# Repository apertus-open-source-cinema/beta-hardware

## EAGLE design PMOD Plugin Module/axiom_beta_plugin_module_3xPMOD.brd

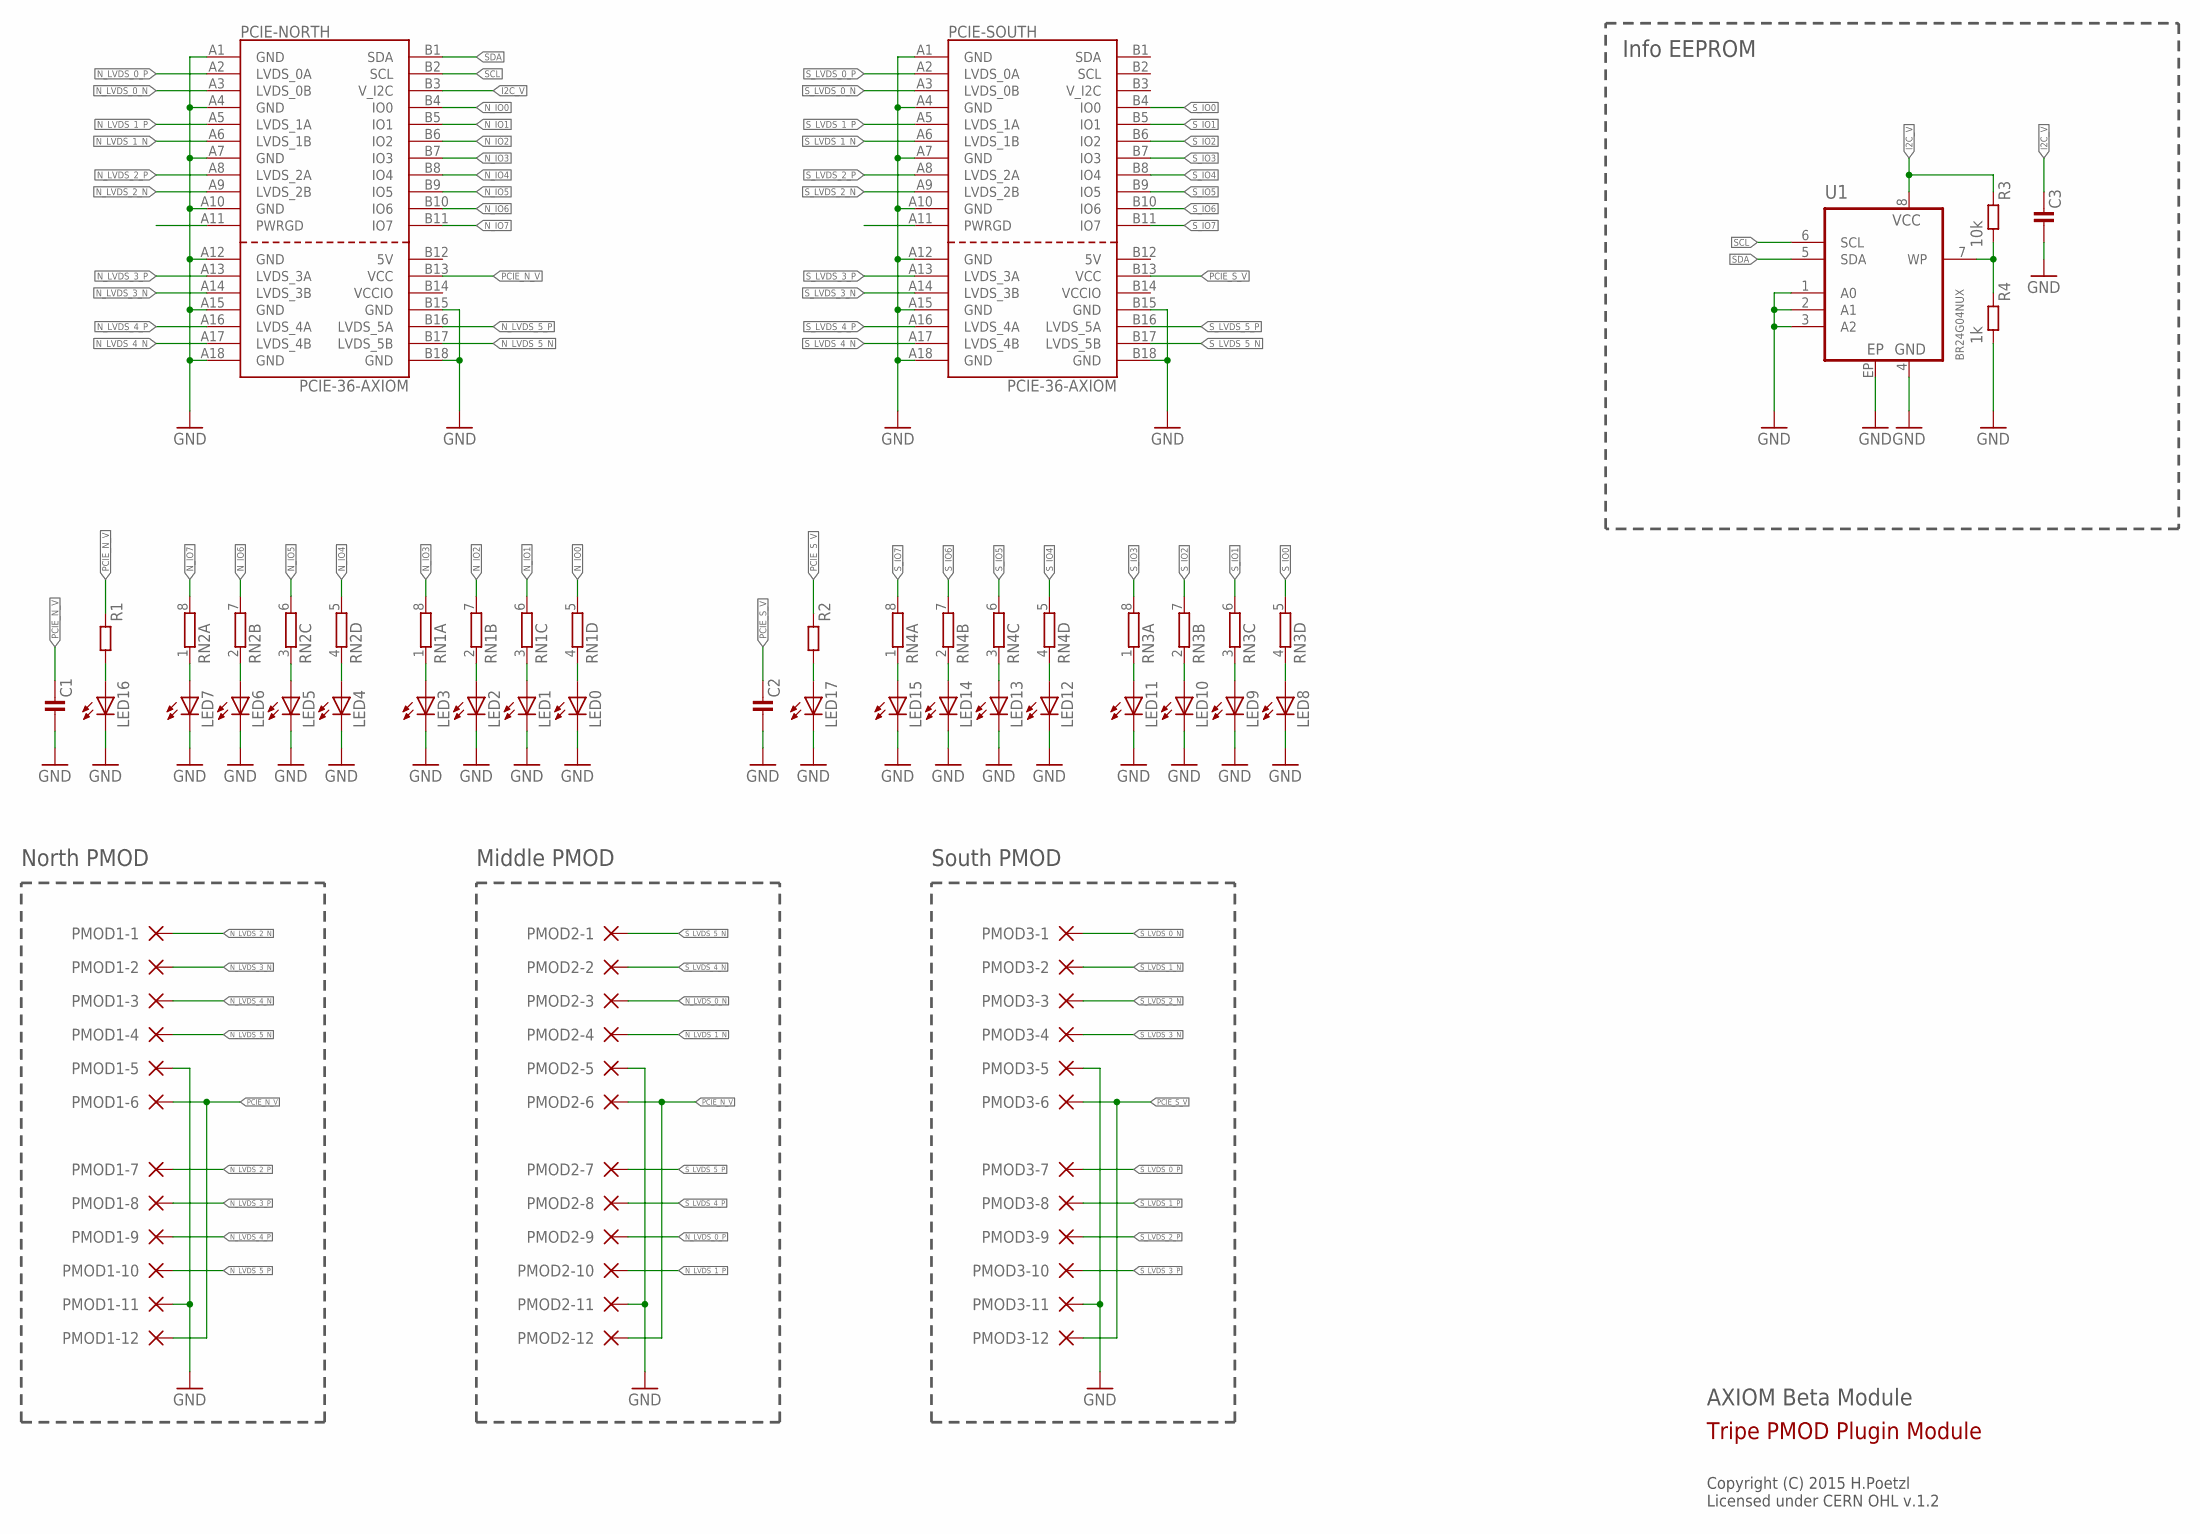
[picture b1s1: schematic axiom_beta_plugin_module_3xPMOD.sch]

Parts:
C1, C2: C1206-A; 1206-A
C3: C0402-B; 0402-B
LED0, LED1, LED2, LED3, LED4, LED5, LED6, LED7, LED8, LED9, LED10, LED11, LED12, LED13, LED14, LED15, LED16, LED17: LEDCHIPLED_0603; CHIPLED_0603
PCIE-NORTH: PCIE-36-AXIOM
PCIE-SOUTH: PCIE-36-AXIOM
PMOD1-1, PMOD1-2, PMOD1-3, PMOD1-4, PMOD1-5, PMOD1-6, PMOD1-7, PMOD1-8, PMOD1-9, PMOD1-10, PMOD1-11, PMOD1-12, PMOD2-1, PMOD2-2, PMOD2-3, PMOD2-4, PMOD2-5, PMOD2-6, PMOD2-7, PMOD2-8, PMOD2-9, PMOD2-10, PMOD2-11, PMOD2-12, PMOD3-1, PMOD3-2, PMOD3-3, PMOD3-4, PMOD3-5, PMOD3-6, PMOD3-7, PMOD3-8, PMOD3-9, PMOD3-10, PMOD3-11, PMOD3-12: SMD-PAD1.6X3.8MM-U; 1.6X3.8U-MM
R1, R2: R0402-B; 0402-B
R3: 10k; 0402-B
R4: 1k; 0402-B
RN1, RN2, RN3, RN4: 4R-NCAY16; CAY16
U1: BR24G04NUX; DFN200X300X100-9N

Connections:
GND: C1.2, C2.2, C3.2, LED0.C, LED1.C, LED2.C, LED3.C, LED4.C, LED5.C, LED6.C, LED7.C, LED8.C, LED9.C, LED10.C, LED11.C, LED12.C, LED13.C, LED14.C, LED15.C, LED16.C, LED17.C, PCIE-NORTH.A1 (GND), PCIE-NORTH.A4 (GND), PCIE-NORTH.A7 (GND), PCIE-NORTH.A10 (GND), PCIE-NORTH.A12 (GND), PCIE-NORTH.A15 (GND), PCIE-NORTH.A18 (GND), PCIE-NORTH.B15 (GND), PCIE-NORTH.B18 (GND), PCIE-SOUTH.A1 (GND), PCIE-SOUTH.A4 (GND), PCIE-SOUTH.A7 (GND), PCIE-SOUTH.A10 (GND), PCIE-SOUTH.A12 (GND), PCIE-SOUTH.A15 (GND), PCIE-SOUTH.A18 (GND), PCIE-SOUTH.B15 (GND), PCIE-SOUTH.B18 (GND), PMOD1-5.1, PMOD1-11.1, PMOD2-5.1, PMOD2-11.1, PMOD3-5.1, PMOD3-11.1, R4.2, U1.1 (A0), U1.2 (A1), U1.3 (A2), U1.4 (GND), U1.EP
I2C_V: C3.1, PCIE-NORTH.B3 (V_I2C), R3.1, U1.8 (VCC)
unnamed: LED3.A, RN1.1
unnamed: LED2.A, RN1.2 (1)
unnamed: LED1.A, RN1.3 (1)
unnamed: LED0.A, RN1.4 (1)
unnamed: LED16.A, R1.2
unnamed: LED17.A, R2.2
unnamed: R3.2, R4.1, U1.7 (WP)
unnamed: LED7.A, RN2.1
unnamed: LED6.A, RN2.2 (1)
unnamed: LED5.A, RN2.3 (1)
unnamed: LED4.A, RN2.4 (1)
unnamed: LED11.A, RN3.1
unnamed: LED10.A, RN3.2 (1)
unnamed: LED9.A, RN3.3 (1)
unnamed: LED8.A, RN3.4 (1)
unnamed: LED15.A, RN4.1
unnamed: LED14.A, RN4.2 (1)
unnamed: LED13.A, RN4.3 (1)
unnamed: LED12.A, RN4.4 (1)
N_IO0: PCIE-NORTH.B4 (IO0), RN1.5 (2)
N_IO1: PCIE-NORTH.B5 (IO1), RN1.6 (2)
N_IO2: PCIE-NORTH.B6 (IO2), RN1.7 (2)
N_IO3: PCIE-NORTH.B7 (IO3), RN1.8 (2)
N_IO4: PCIE-NORTH.B8 (IO4), RN2.5 (2)
N_IO5: PCIE-NORTH.B9 (IO5), RN2.6 (2)
N_IO6: PCIE-NORTH.B10 (IO6), RN2.7 (2)
N_IO7: PCIE-NORTH.B11 (IO7), RN2.8 (2)
N_LVDS_0_N: PCIE-NORTH.A3 (LVDS_0B), PMOD2-3.1
N_LVDS_0_P: PCIE-NORTH.A2 (LVDS_0A), PMOD2-9.1
N_LVDS_1_N: PCIE-NORTH.A6 (LVDS_1B), PMOD2-4.1
N_LVDS_1_P: PCIE-NORTH.A5 (LVDS_1A), PMOD2-10.1
N_LVDS_2_N: PCIE-NORTH.A9 (LVDS_2B), PMOD1-1.1
N_LVDS_2_P: PCIE-NORTH.A8 (LVDS_2A), PMOD1-7.1
N_LVDS_3_N: PCIE-NORTH.A14 (LVDS_3B), PMOD1-2.1
N_LVDS_3_P: PCIE-NORTH.A13 (LVDS_3A), PMOD1-8.1
N_LVDS_4_N: PCIE-NORTH.A17 (LVDS_4B), PMOD1-3.1
N_LVDS_4_P: PCIE-NORTH.A16 (LVDS_4A), PMOD1-9.1
N_LVDS_5_N: PCIE-NORTH.B17 (LVDS_5B), PMOD1-4.1
N_LVDS_5_P: PCIE-NORTH.B16 (LVDS_5A), PMOD1-10.1
PCIE_N_V: C1.1, PCIE-NORTH.B13 (VCC), PMOD1-6.1, PMOD1-12.1, PMOD2-6.1, PMOD2-12.1, R1.1
PCIE_S_V: C2.1, PCIE-SOUTH.B13 (VCC), PMOD3-6.1, PMOD3-12.1, R2.1
SCL: PCIE-NORTH.B2 (SCL), U1.6 (SCL)
SDA: PCIE-NORTH.B1 (SDA), U1.5 (SDA)
S_IO0: PCIE-SOUTH.B4 (IO0), RN3.5 (2)
S_IO1: PCIE-SOUTH.B5 (IO1), RN3.6 (2)
S_IO2: PCIE-SOUTH.B6 (IO2), RN3.7 (2)
S_IO3: PCIE-SOUTH.B7 (IO3), RN3.8 (2)
S_IO4: PCIE-SOUTH.B8 (IO4), RN4.5 (2)
S_IO5: PCIE-SOUTH.B9 (IO5), RN4.6 (2)
S_IO6: PCIE-SOUTH.B10 (IO6), RN4.7 (2)
S_IO7: PCIE-SOUTH.B11 (IO7), RN4.8 (2)
S_LVDS_0_N: PCIE-SOUTH.A3 (LVDS_0B), PMOD3-1.1
S_LVDS_0_P: PCIE-SOUTH.A2 (LVDS_0A), PMOD3-7.1
S_LVDS_1_N: PCIE-SOUTH.A6 (LVDS_1B), PMOD3-2.1
S_LVDS_1_P: PCIE-SOUTH.A5 (LVDS_1A), PMOD3-8.1
S_LVDS_2_N: PCIE-SOUTH.A9 (LVDS_2B), PMOD3-3.1
S_LVDS_2_P: PCIE-SOUTH.A8 (LVDS_2A), PMOD3-9.1
S_LVDS_3_N: PCIE-SOUTH.A14 (LVDS_3B), PMOD3-4.1
S_LVDS_3_P: PCIE-SOUTH.A13 (LVDS_3A), PMOD3-10.1
S_LVDS_4_N: PCIE-SOUTH.A17 (LVDS_4B), PMOD2-2.1
S_LVDS_4_P: PCIE-SOUTH.A16 (LVDS_4A), PMOD2-8.1
S_LVDS_5_N: PCIE-SOUTH.B17 (LVDS_5B), PMOD2-1.1
S_LVDS_5_P: PCIE-SOUTH.B16 (LVDS_5A), PMOD2-7.1

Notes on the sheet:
AXIOM Beta Module
Copyright (C) 2015 H.Poetzl Licensed under CERN OHL v.1.2
Tripe PMOD Plugin Module
Info EEPROM
North PMOD
Middle PMOD
South PMOD

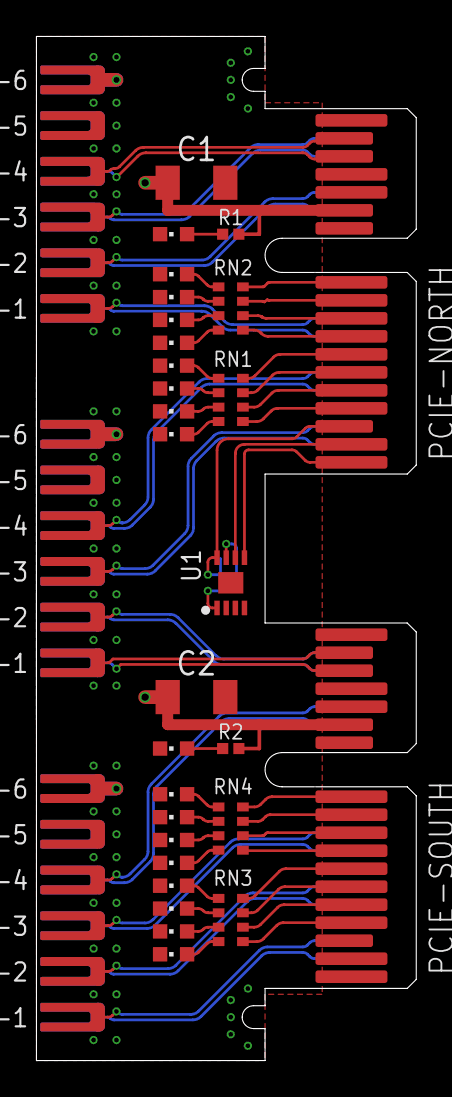
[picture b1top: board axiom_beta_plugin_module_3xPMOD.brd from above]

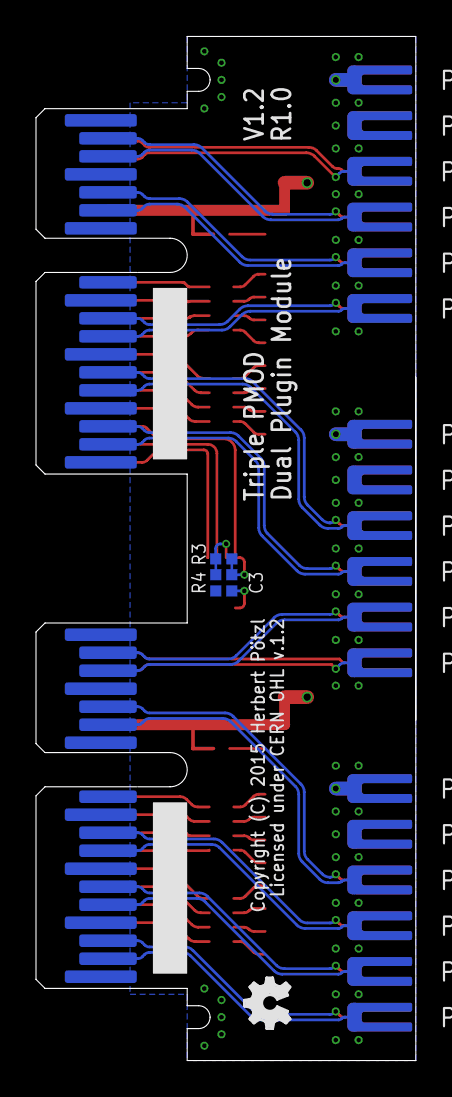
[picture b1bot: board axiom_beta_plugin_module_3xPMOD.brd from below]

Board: 4 copper layers, 21.1 x 56.9 mm, 69 parts (22 on the bottom side), 65 nets.

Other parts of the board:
LOGO1: OSHW_LOGO_FILLX0100-NT; OSHW_FILLX100_NOTEXT

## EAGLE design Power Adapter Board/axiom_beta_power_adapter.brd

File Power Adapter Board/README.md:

# AXIOM Beta Power Adapter Board v0.2

https://wiki.apertus.org/index.php/Beta_Power_Adapter_Board

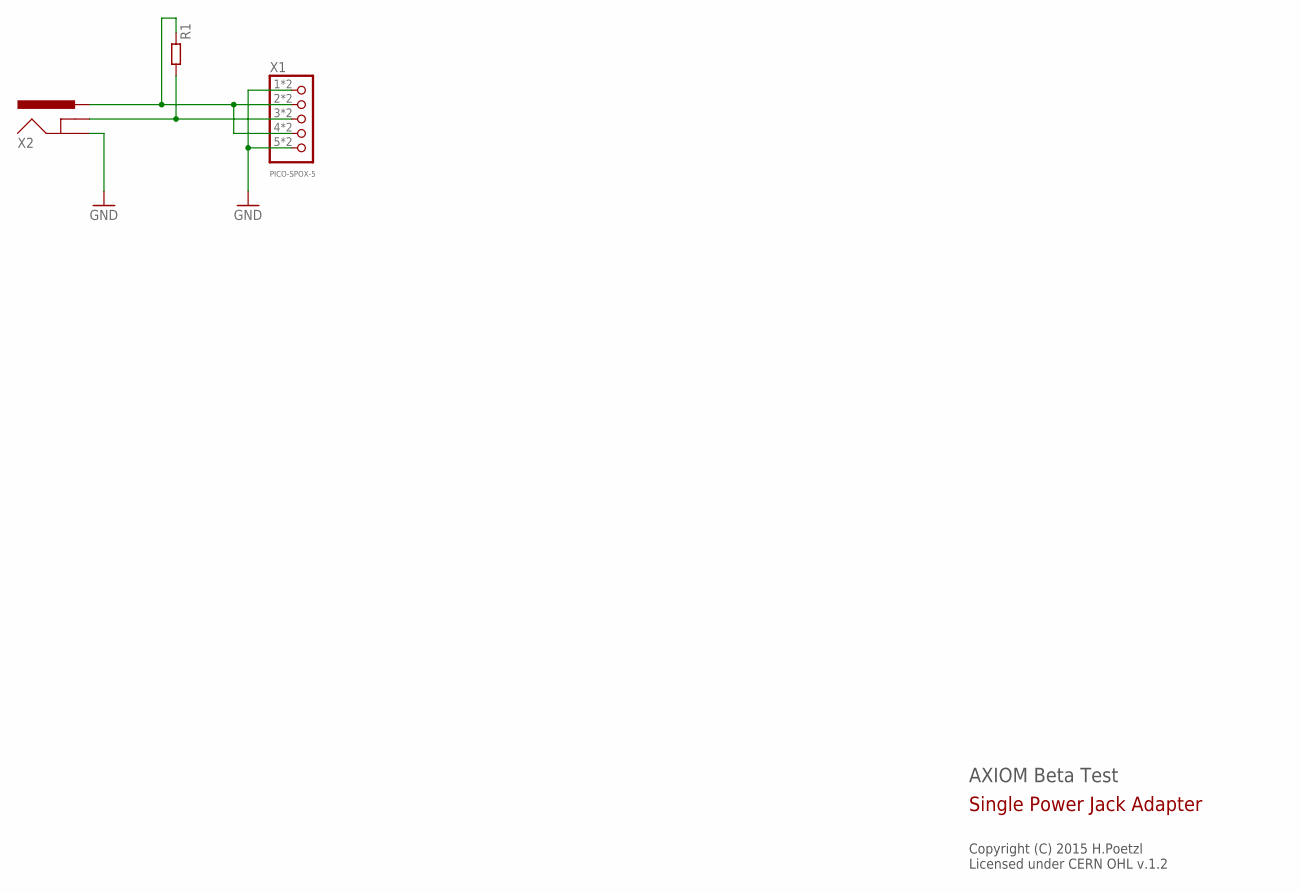
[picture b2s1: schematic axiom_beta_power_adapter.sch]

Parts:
R1: R0402-B; 0402-B
X1: PICO-SPOX-5
X2: POWER_JACKPTH_N; POWER_JACK_PTH_NARROW

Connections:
BETA_5V: R1.1, X1.2, X1.2A (2), X1.4, X1.4A (4), X2.PWR
GND: X1.1, X1.1A (1), X1.5, X1.5A (5), X2.GND
VIN: R1.2, X1.3, X1.3A (3), X2.SHUNT (GNDBREAK)

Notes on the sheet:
AXIOM Beta Test
Copyright (C) 2015 H.Poetzl Licensed under CERN OHL v.1.2
Single Power Jack Adapter

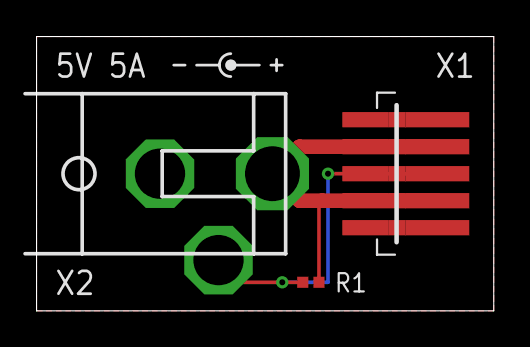
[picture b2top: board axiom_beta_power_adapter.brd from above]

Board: 2 copper layers, 25.4 x 15.2 mm, 4 parts (1 on the bottom side), 3 nets.

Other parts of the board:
LOGO1: OSHW_LOGO_FILLX0100-NT; OSHW_FILLX100_NOTEXT

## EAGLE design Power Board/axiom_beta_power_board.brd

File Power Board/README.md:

# AXIOM Beta Power Board v0.30

https://wiki.apertus.org/index.php/Beta_Power_Board

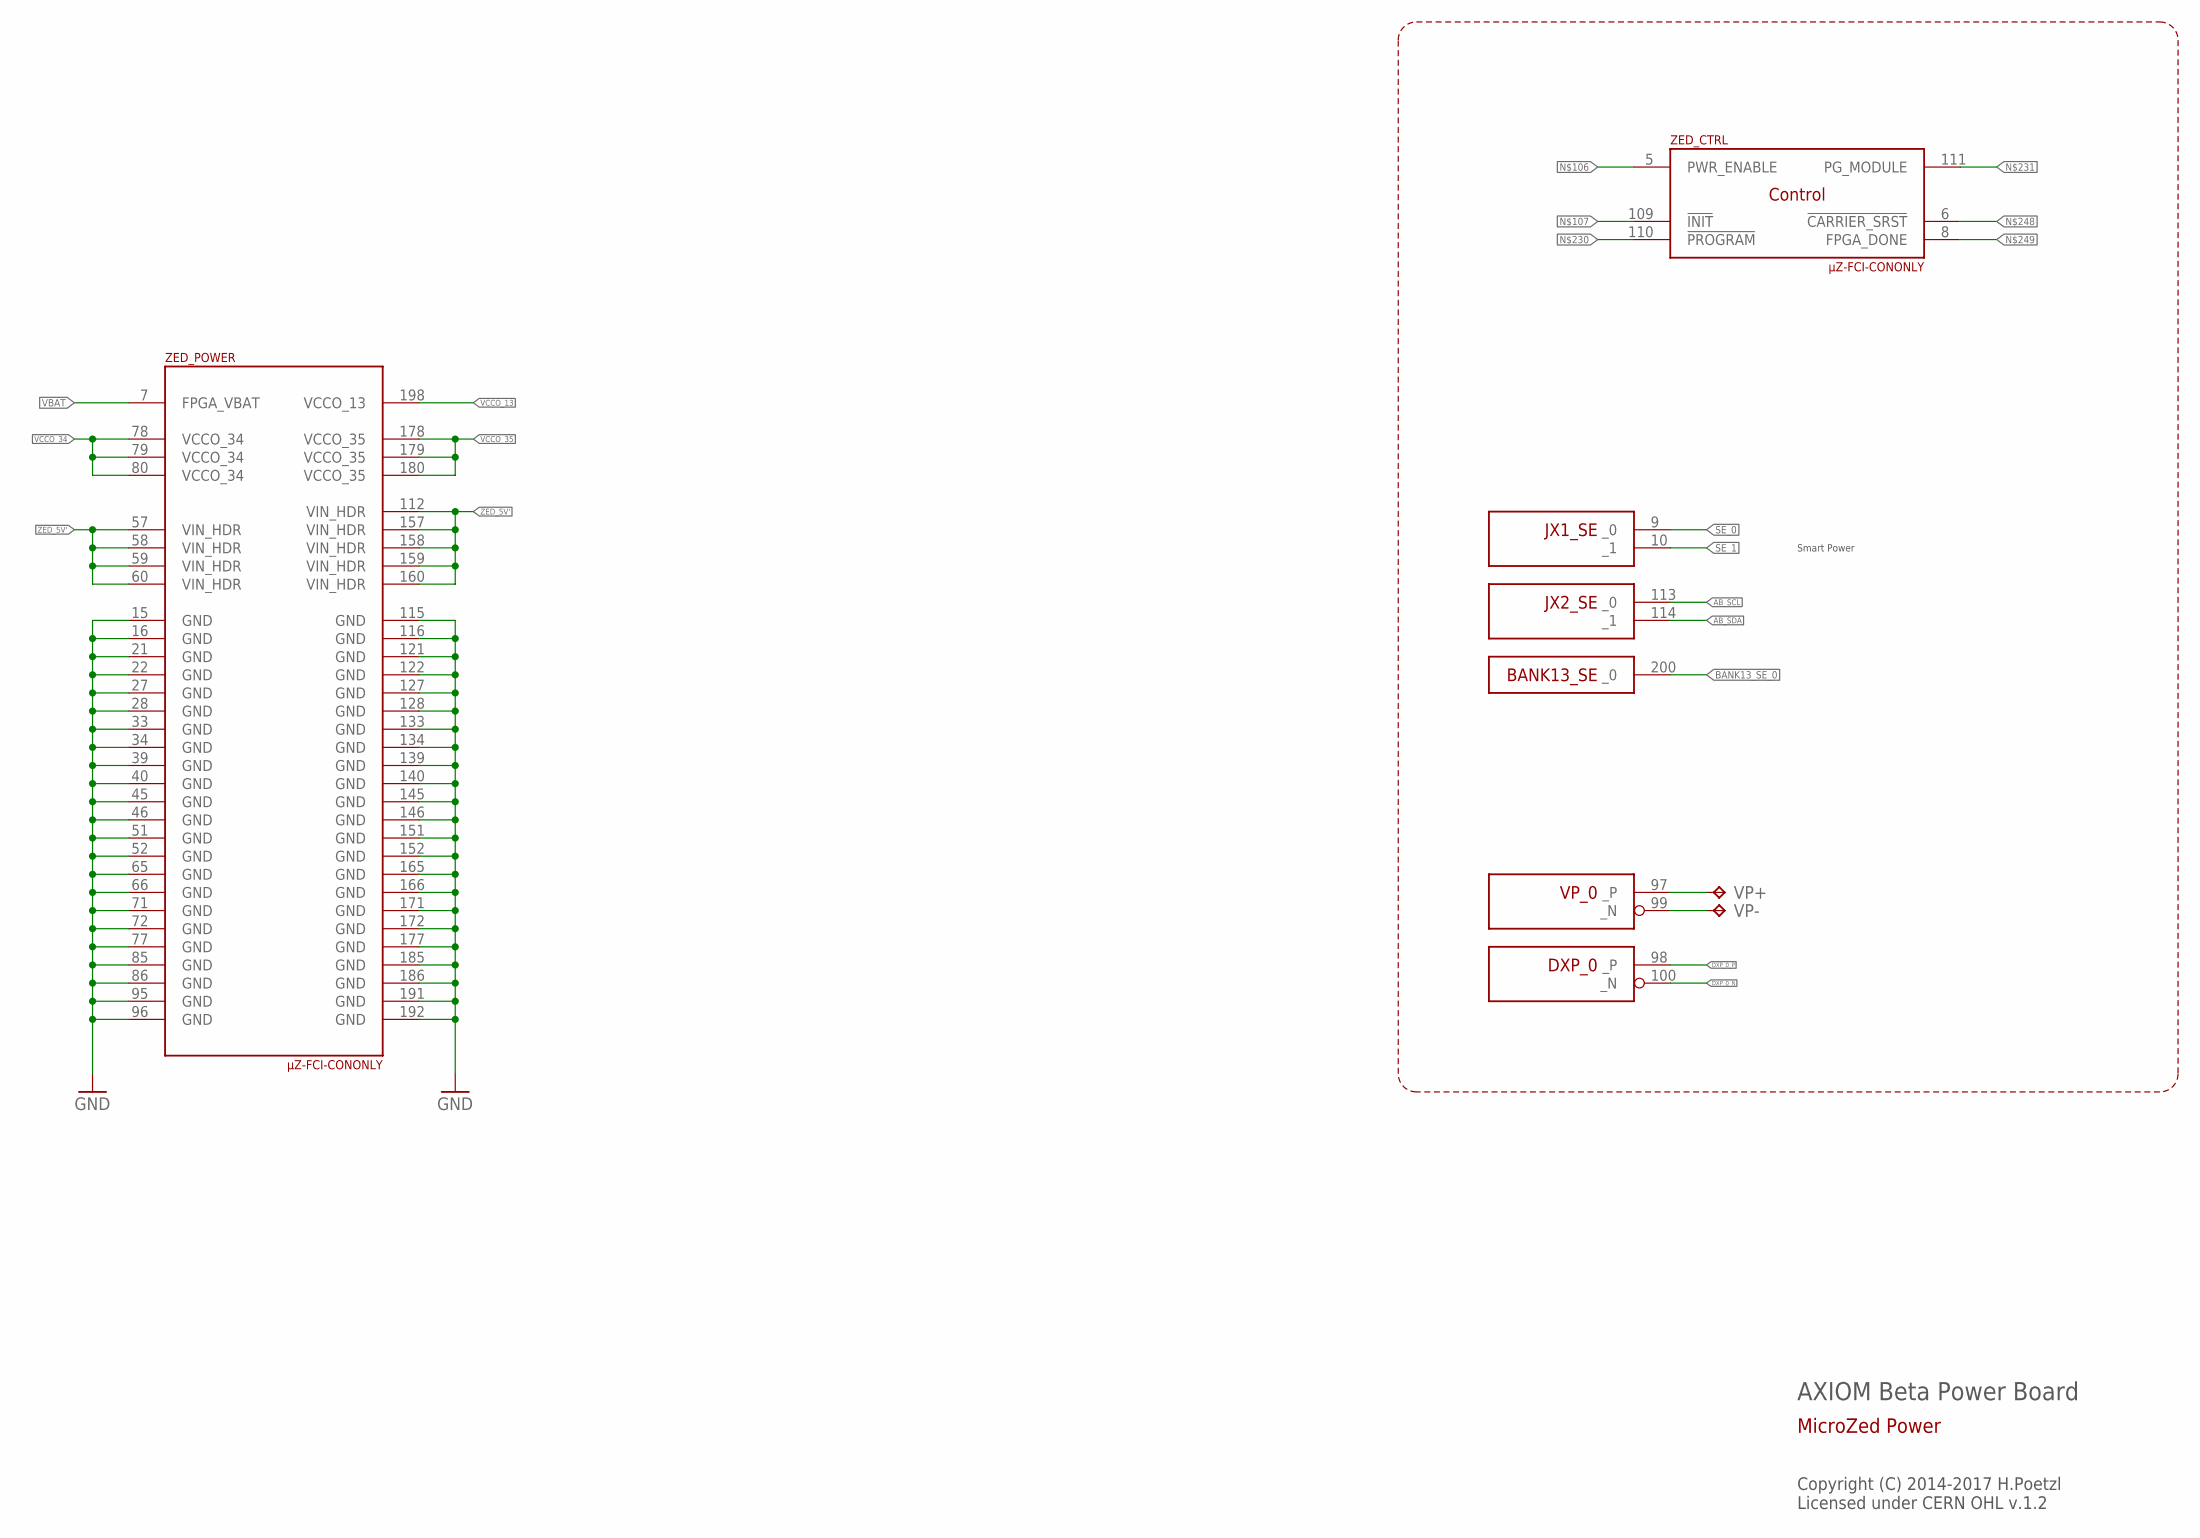
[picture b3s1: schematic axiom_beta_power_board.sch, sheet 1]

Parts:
VP+: TPTP16SQ; TP16SQ
VP-: TPTP16SQ; TP16SQ
ZED: µZ-FCI-CONONLY; µZ-CONONLY

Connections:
AB_SCL: ZED.113 (_0); also elsewhere on the board
AB_SDA: ZED.114 (_1); also elsewhere on the board
BANK13_SE_0: ZED.200 (_0); also elsewhere on the board
DXP_0_N: ZED.100 (_N)
DXP_0_P: ZED.98 (_P)
GND: ZED.15 (GND), ZED.16 (GND), ZED.21 (GND), ZED.22 (GND), ZED.27 (GND), ZED.28 (GND), ZED.33 (GND), ZED.34 (GND), ZED.39 (GND), ZED.40 (GND), ZED.45 (GND), ZED.46 (GND), ZED.51 (GND), ZED.52 (GND), ZED.65 (GND), ZED.66 (GND), ZED.71 (GND), ZED.72 (GND), ZED.77 (GND), ZED.85 (GND), ZED.86 (GND), ZED.95 (GND), ZED.96 (GND), ZED.115 (GND), ZED.116 (GND), ZED.121 (GND), ZED.122 (GND), ZED.127 (GND), ZED.128 (GND), ZED.133 (GND), ZED.134 (GND), ZED.139 (GND), ZED.140 (GND), ZED.145 (GND), ZED.146 (GND), ZED.151 (GND), ZED.152 (GND), ZED.165 (GND), ZED.166 (GND), ZED.171 (GND), ZED.172 (GND), ZED.177 (GND), ZED.185 (GND), ZED.186 (GND), ZED.191 (GND), ZED.192 (GND); also elsewhere on the board
SE_0: ZED.9 (_0); also elsewhere on the board
SE_1: ZED.10 (_1); also elsewhere on the board
VBAT: ZED.7 (FPGA_VBAT)
VCCO_13: ZED.198 (VCCO_13); also elsewhere on the board
VCCO_34: ZED.78 (VCCO_34), ZED.79 (VCCO_34), ZED.80 (VCCO_34); also elsewhere on the board
VCCO_35: ZED.178 (VCCO_35), ZED.179 (VCCO_35), ZED.180 (VCCO_35); also elsewhere on the board
VP_0_N: VP-.TP, ZED.99 (_N)
VP_0_P: VP+.TP, ZED.97 (_P)
ZED_5V': ZED.57 (VIN_HDR), ZED.58 (VIN_HDR), ZED.59 (VIN_HDR), ZED.60 (VIN_HDR), ZED.112 (VIN_HDR), ZED.157 (VIN_HDR), ZED.158 (VIN_HDR), ZED.159 (VIN_HDR), ZED.160 (VIN_HDR); also elsewhere on the board

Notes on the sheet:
AXIOM Beta Power Board
Copyright (C) 2014-2017 H.Poetzl Licensed under CERN OHL v.1.2
MicroZed Power
Smart Power

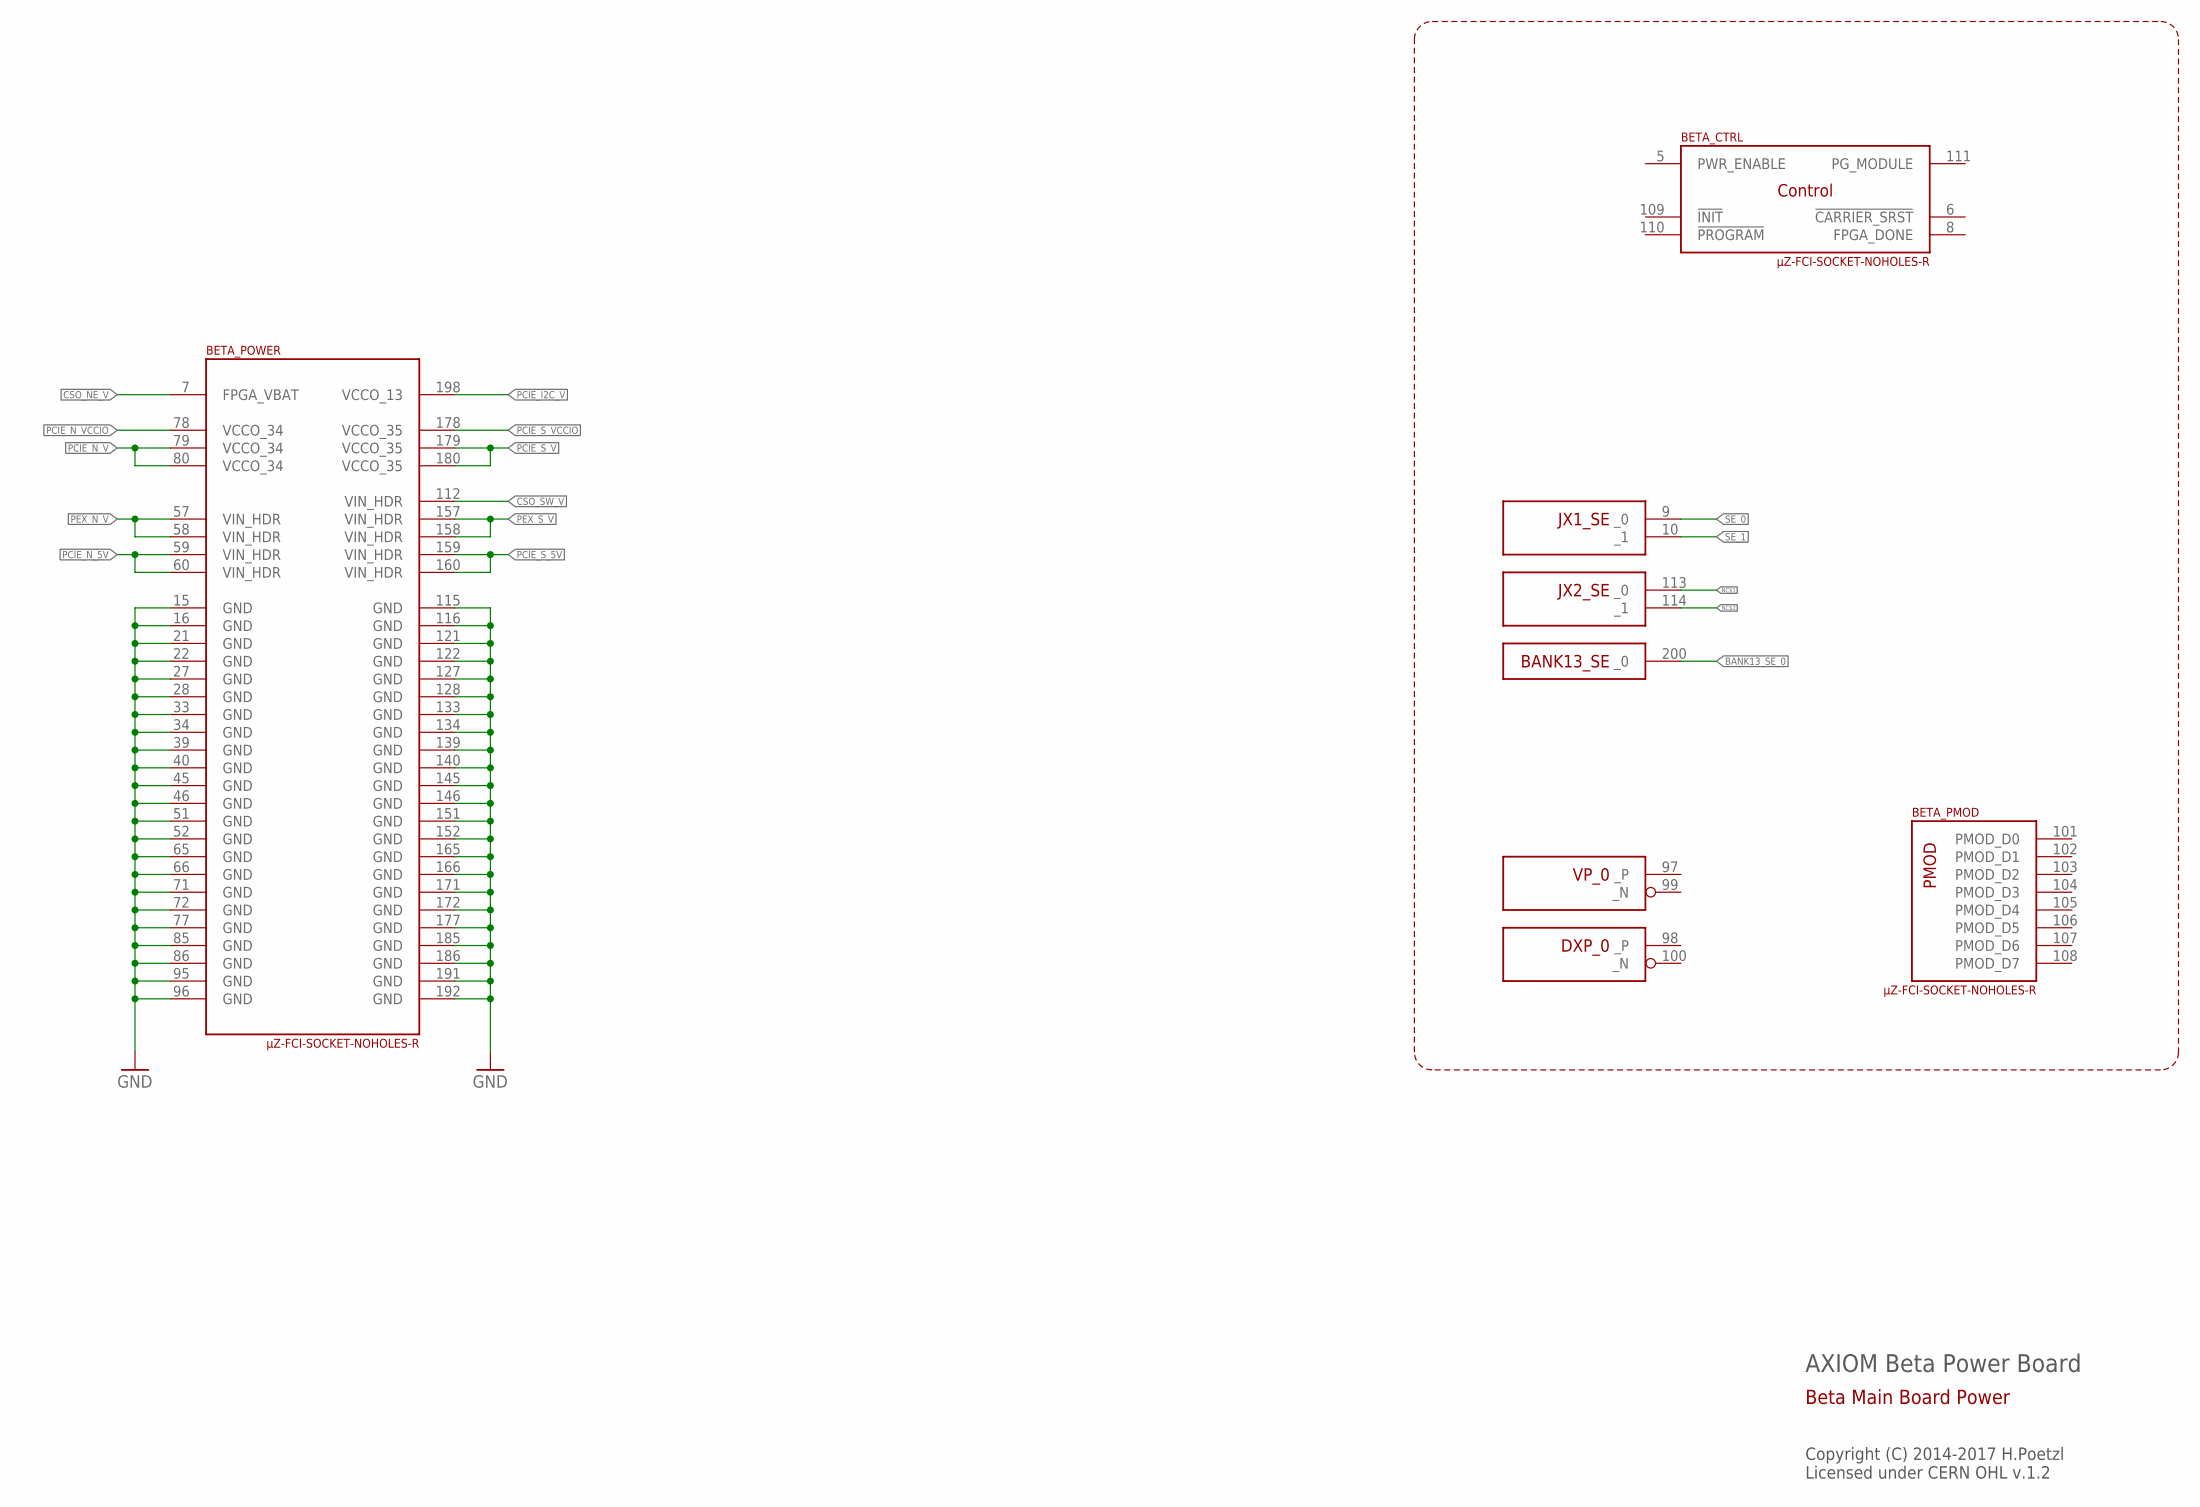
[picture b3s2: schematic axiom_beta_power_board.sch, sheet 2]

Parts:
BETA: µZ-FCI-SOCKET-NOHOLES-R; µZ-SOCKET-NOHOLES-R

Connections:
BANK13_SE_0: BETA.200 (_0); also elsewhere on the board
CSO_NE_V: BETA.7 (FPGA_VBAT); also elsewhere on the board
CSO_SW_V: BETA.112 (VIN_HDR); also elsewhere on the board
GND: BETA.15 (GND), BETA.16 (GND), BETA.21 (GND), BETA.22 (GND), BETA.27 (GND), BETA.28 (GND), BETA.33 (GND), BETA.34 (GND), BETA.39 (GND), BETA.40 (GND), BETA.45 (GND), BETA.46 (GND), BETA.51 (GND), BETA.52 (GND), BETA.65 (GND), BETA.66 (GND), BETA.71 (GND), BETA.72 (GND), BETA.77 (GND), BETA.85 (GND), BETA.86 (GND), BETA.95 (GND), BETA.96 (GND), BETA.115 (GND), BETA.116 (GND), BETA.121 (GND), BETA.122 (GND), BETA.127 (GND), BETA.128 (GND), BETA.133 (GND), BETA.134 (GND), BETA.139 (GND), BETA.140 (GND), BETA.145 (GND), BETA.146 (GND), BETA.151 (GND), BETA.152 (GND), BETA.165 (GND), BETA.166 (GND), BETA.171 (GND), BETA.172 (GND), BETA.177 (GND), BETA.185 (GND), BETA.186 (GND), BETA.191 (GND), BETA.192 (GND); also elsewhere on the board
NC$1: BETA.113 (_0)
NC$2: BETA.114 (_1)
PCIE_I2C_V: BETA.198 (VCCO_13)
PCIE_N_5V: BETA.59 (VIN_HDR), BETA.60 (VIN_HDR)
PCIE_N_V: BETA.79 (VCCO_34), BETA.80 (VCCO_34); also elsewhere on the board
PCIE_N_VCCIO: BETA.78 (VCCO_34)
PCIE_S_5V: BETA.159 (VIN_HDR), BETA.160 (VIN_HDR)
PCIE_S_V: BETA.179 (VCCO_35), BETA.180 (VCCO_35); also elsewhere on the board
PCIE_S_VCCIO: BETA.178 (VCCO_35)
PEX_N_V: BETA.57 (VIN_HDR), BETA.58 (VIN_HDR)
PEX_S_V: BETA.157 (VIN_HDR), BETA.158 (VIN_HDR)
SE_0: BETA.9 (_0); also elsewhere on the board
SE_1: BETA.10 (_1); also elsewhere on the board

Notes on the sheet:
AXIOM Beta Power Board
Copyright (C) 2014-2017 H.Poetzl Licensed under CERN OHL v.1.2
Beta Main Board Power

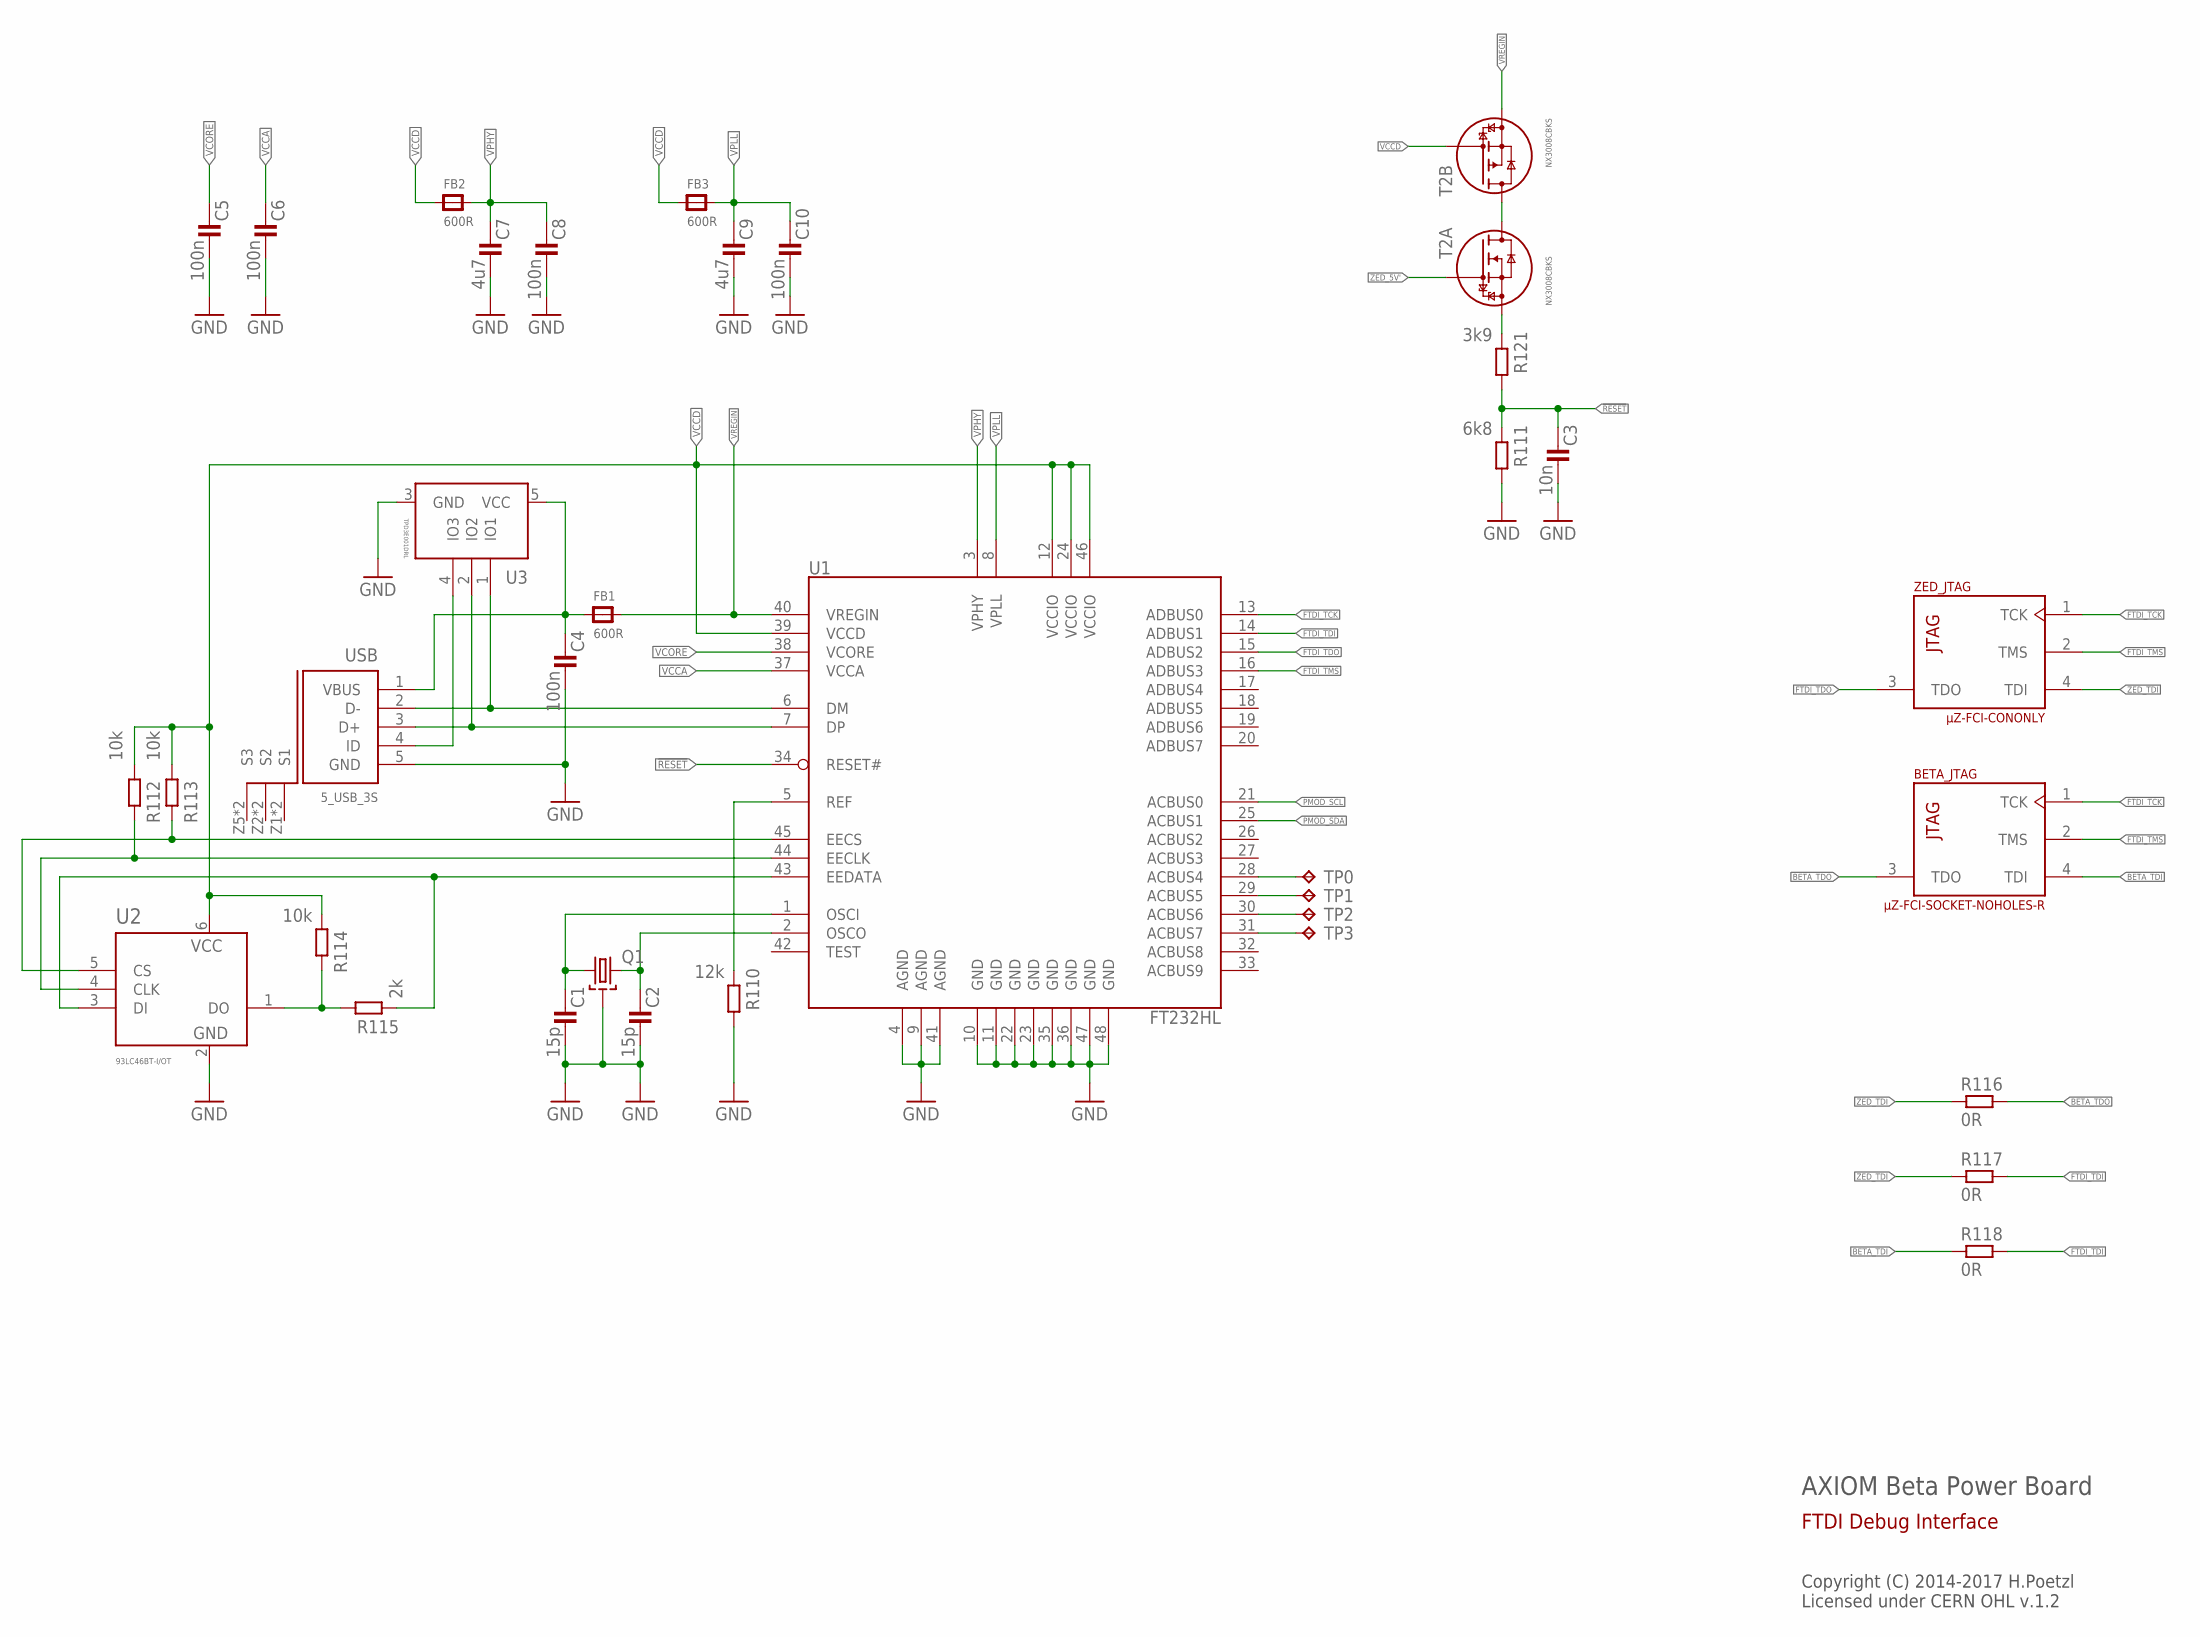
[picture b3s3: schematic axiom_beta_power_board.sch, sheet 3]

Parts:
BETA: µZ-FCI-SOCKET-NOHOLES-R; µZ-SOCKET-NOHOLES-R
C1, C2: 15p; 0402-B
C3: 10n; 0402-B
C4: 100n; 0603-B
C5, C6, C8, C10: 100n; 0402-B
C7, C9: 4u7; 0603-B
FB1, FB2, FB3: 600R; _0603MP
Q1: SMD-4P-2G-3.2X2.5; ABM8G
R110: 12k; 0402-B
R111: 6k8; 0402-B
R112, R113, R114: 10k; 0402-B
R115: 2k; 0402-B
R116, R117, R118: 0R; 0402-B
R121: 3k9; 0402-B
T2: NX3008CBKS; SOT363
TP0, TP1, TP2, TP3: TPTP16SQ; TP16SQ
U1: FT232HL; LQFP48
U2: 93LC46BT-I/OT; SOT95P280X145-6N
U3: TPD3E001DRL; R-PDSO-N5
USB: 5_USB_3S; MICRO-AB-H-SMT
ZED: µZ-FCI-CONONLY; µZ-CONONLY

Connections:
!RESET: C3.1, R111.2, R121.1, U1.34 (RESET#)
BETA_TDI: BETA.4 (TDI), R118.2
BETA_TDO: BETA.3 (TDO), R116.1
EE_CLK1: R112.1, U1.44 (EECLK), U2.4 (CLK)
EE_CS1: R113.1, U1.45 (EECS), U2.5 (CS)
EE_DATA1: R115.2, U1.43 (EEDATA), U2.3 (DI)
FTDI_D_N: U1.6 (DM), U3.1 (IO1), USB.2 (D-)
FTDI_D_P: U1.7 (DP), U3.2 (IO2), USB.3 (D+)
FTDI_TCK: BETA.1 (TCK), U1.13 (ADBUS0), ZED.1 (TCK)
FTDI_TDI: R117.1, R118.1, U1.14 (ADBUS1)
FTDI_TDO: U1.15 (ADBUS2), ZED.3 (TDO)
FTDI_TMS: BETA.2 (TMS), U1.16 (ADBUS3), ZED.2 (TMS)
GND: C1.2, C2.2, C3.2, C4.2, C5.2, C6.2, C7.2, C8.2, C9.2, C10.2, Q1.2 (GND), Q1.4 (GND), R110.1, R111.1, U1.4 (AGND), U1.9 (AGND), U1.10 (GND), U1.11 (GND), U1.22 (GND), U1.23 (GND), U1.35 (GND), U1.36 (GND), U1.41 (AGND), U1.47 (GND), U1.48 (GND), U2.2 (VSS), U3.3 (GND), USB.5 (GND); also elsewhere on the board
unnamed: C4.1, FB1.1, U3.5 (VCC), USB.1 (VBUS)
unnamed: R121.2, T2.1 (S)
unnamed: TP0.TP, U1.28 (ACBUS4)
unnamed: TP1.TP, U1.29 (ACBUS5)
unnamed: TP2.TP, U1.30 (ACBUS6)
unnamed: TP3.TP, U1.31 (ACBUS7)
unnamed: T2.3 (D), T2.6 (D)
unnamed: R114.1, R115.1, U2.1 (DO)
unnamed: C1.1, Q1.1, U1.1 (OSCI)
unnamed: C2.1, Q1.3 (2), U1.2 (OSCO)
unnamed: R110.2, U1.5 (REF)
unnamed: U3.4 (IO3), USB.4 (ID)
PMOD_SCL: U1.21 (ACBUS0); also elsewhere on the board
PMOD_SDA: U1.25 (ACBUS1); also elsewhere on the board
VCCA: C6.1, U1.37 (VCCA)
VCCD: FB2.1, FB3.1, R112.2, R113.2, R114.2, T2.5 (G), U1.12 (VCCIO), U1.24 (VCCIO), U1.39 (VCCD), U1.46 (VCCIO), U2.6 (VCC)
VCORE: C5.1, U1.38 (VCORE)
VPHY: C7.1, C8.1, FB2.2, U1.3 (VPHY)
VPLL: C9.1, C10.1, FB3.2, U1.8 (VPLL)
VREGIN: FB1.2, T2.4 (S), U1.40 (VREGIN)
ZED_5V': T2.2 (G); also elsewhere on the board
ZED_TDI: R116.2, R117.2, ZED.4 (TDI)

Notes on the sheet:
AXIOM Beta Power Board
Copyright (C) 2014-2017 H.Poetzl Licensed under CERN OHL v.1.2
FTDI Debug Interface

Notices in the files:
PMOD Plugin Module/axiom_beta_plugin_module_3xPMOD.brd:
Copyright (C) 2015 Herbert Pötzl
Power Board/axiom_beta_power_board.brd:
Copyright (C) 2015-2017 Herbert Pötzl
USB 3.0 Plugin Module/axiom_beta_plugin_module_1xUSB30.brd:
(C) 2017 H.Pötzl
Licensed under
CERN OHL v.1.2
parts and their libraries:
microbuilder: This work is placed in the public domain, and may be freely used for commercial and non-commercial work with the following conditions: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
